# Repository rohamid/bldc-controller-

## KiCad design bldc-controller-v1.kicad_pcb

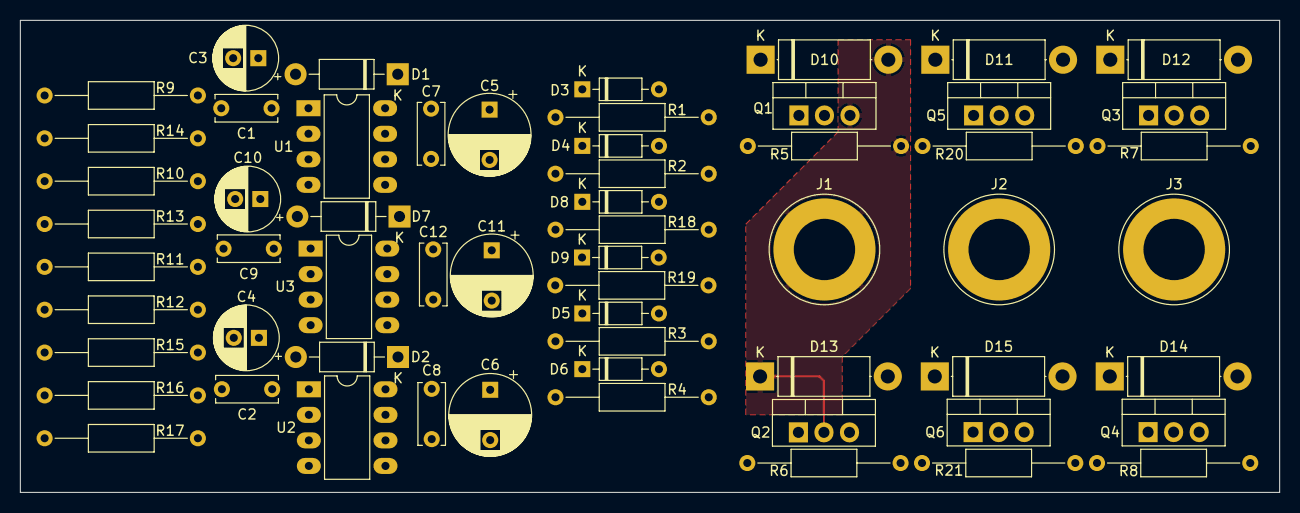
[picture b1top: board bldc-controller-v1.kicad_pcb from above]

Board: 2 copper layers, 125.2 x 46.9 mm, 60 parts (0 on the bottom side), 25 nets.

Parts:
C1, C2, C9: 100n; C_Disc_D6.0mm_W2.5mm_P5.00mm
C3, C4, C10: 10u; CP_Radial_D6.3mm_P2.50mm
C5, C6, C11: 10u; CP_Radial_D8.0mm_P5.00mm
C7, C8, C12: 1u; C_Disc_D6.0mm_W2.5mm_P5.00mm
D1, D2, D7: 1N5819; D_DO-41_SOD81_P10.16mm_Horizontal
D3, D4, D5, D6, D8, D9: 1N4148; D_DO-35_SOD27_P7.62mm_Horizontal
D10, D11, D12, D13, D14, D15: SS34; D_5W_P12.70mm_Horizontal
J1, J2, J3: Conn_01x01_Socket; Banana_Jack_1Pin
Q1, Q2, Q3, Q4, Q5, Q6: IRF3205; TO-220-3_Vertical
R1, R2, R3, R4, R18, R19: 10; R_Axial_DIN0207_L6.3mm_D2.5mm_P15.24mm_Horizontal
R5, R6, R7, R8, R20, R21: 10K; R_Axial_DIN0207_L6.3mm_D2.5mm_P15.24mm_Horizontal
R9, R10, R11, R12, R13, R14, R15, R16, R17: 33K; R_Axial_DIN0207_L6.3mm_D2.5mm_P15.24mm_Horizontal
U1, U2, U3: IR2101; DIP-8_W7.62mm_LongPads

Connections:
/MOSFET/BEMF_A: R9.2, R14.2, R15.1
/MOSFET/BEMF_B: R10.2, R13.2, R16.1
/MOSFET/BEMF_C: R11.2, R12.2, R17.1
/MOSFET/PHASE_A: C5.2, C7.2, D10.2 (A), D13.1 (K), J1.1, Q1.3 (S), Q2.2 (D), R5.1, R9.1, U1.6 (VS)
/MOSFET/PHASE_B: C11.2, C12.2, D11.2 (A), D15.1 (K), J2.1, Q5.3 (S), Q6.2 (D), R10.1, R20.1, U3.6 (VS)
/MOSFET/PHASE_C: C6.2, C8.2, D12.2 (A), D14.1 (K), J3.1, Q3.3 (S), Q4.2 (D), R7.1, R11.1, U2.6 (VS)
/MOSFET/PHASE_VGND: R15.2, R16.2, R17.2
GND: C1.2, C2.2, C3.2, C4.2, C9.2, C10.2, D13.2 (A), D14.2 (A), D15.2 (A), Q2.3 (S), Q4.3 (S), Q6.3 (S), R6.1, R8.1, R12.1, R13.1, R14.1, R21.1, U1.4 (COM), U2.4 (COM), U3.4 (COM)
unnamed: C5.1, C7.1, D1.1 (K), U1.8 (VB)
unnamed: C6.1, C8.1, D2.1 (K), U2.8 (VB)
unnamed: D3.2 (A), Q1.1 (G), R1.2, R5.2
unnamed: D3.1 (K), R1.1, U1.7 (HO)
unnamed: D4.2 (A), Q2.1 (G), R2.2, R6.2
unnamed: D4.1 (K), R2.1, U1.5 (LO)
unnamed: D5.2 (A), Q3.1 (G), R3.2, R7.2
unnamed: D5.1 (K), R3.1, U2.7 (HO)
unnamed: D6.2 (A), Q4.1 (G), R4.2, R8.2
unnamed: D6.1 (K), R4.1, U2.5 (LO)
unnamed: C11.1, C12.1, D7.1 (K), U3.8 (VB)
unnamed: D8.2 (A), Q5.1 (G), R18.2, R20.2
unnamed: D8.1 (K), R18.1, U3.7 (HO)
unnamed: D9.2 (A), Q6.1 (G), R19.2, R21.2
unnamed: D9.1 (K), R19.1, U3.5 (LO)
VDC: D10.1 (K), D11.1 (K), D12.1 (K), Q1.2 (D), Q3.2 (D), Q5.2 (D)
VDD: C1.1, C2.1, C3.1, C4.1, C9.1, C10.1, D1.2 (A), D2.2 (A), D7.2 (A), U1.1 (VCC), U2.1 (VCC), U3.1 (VCC)
